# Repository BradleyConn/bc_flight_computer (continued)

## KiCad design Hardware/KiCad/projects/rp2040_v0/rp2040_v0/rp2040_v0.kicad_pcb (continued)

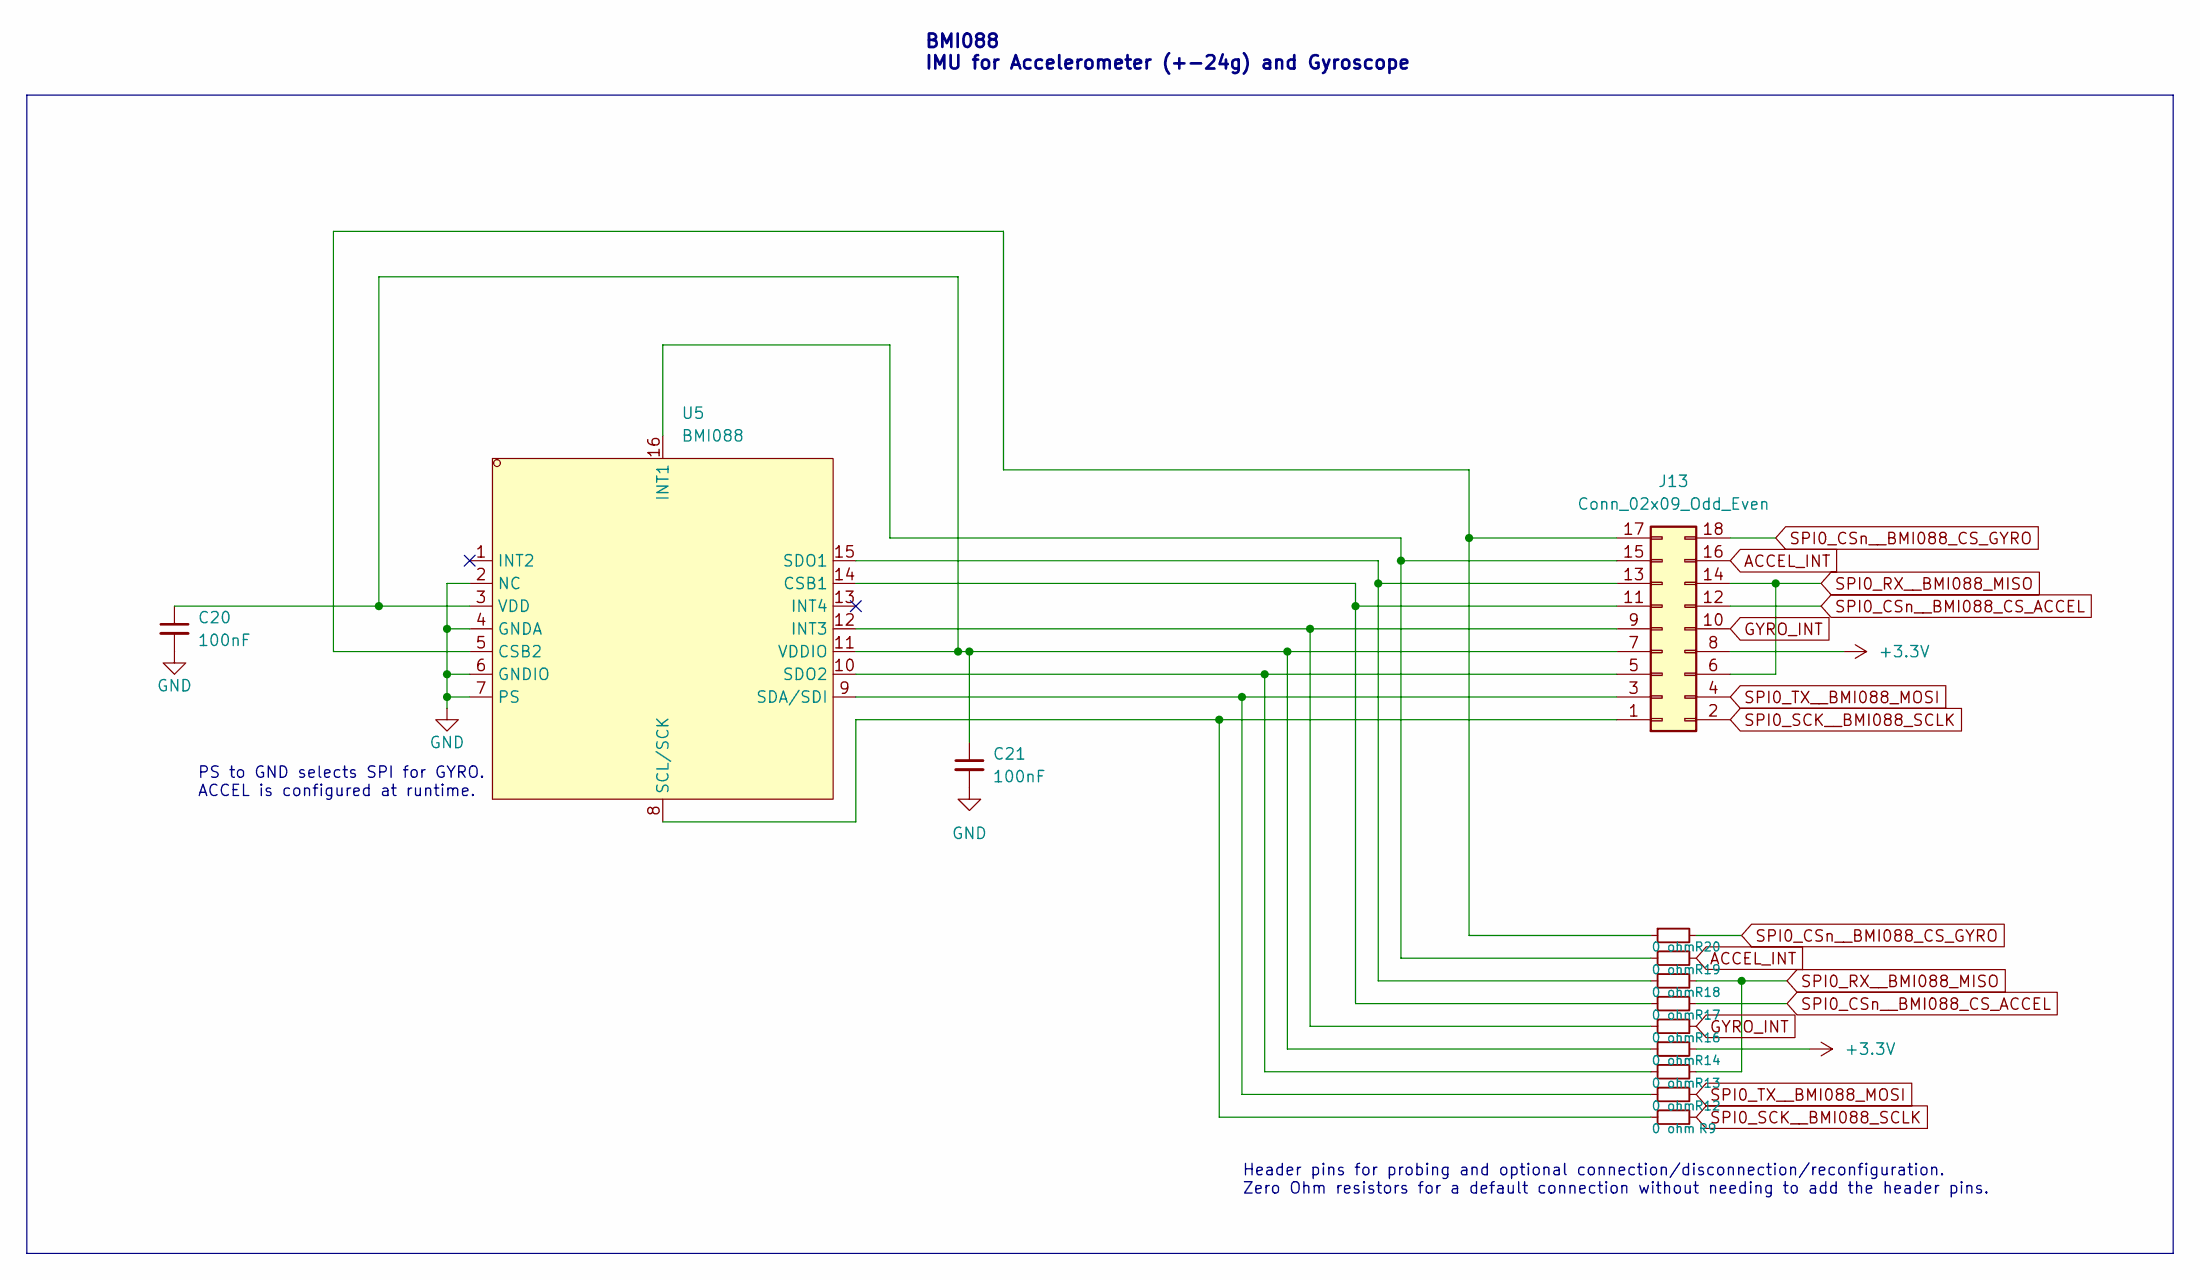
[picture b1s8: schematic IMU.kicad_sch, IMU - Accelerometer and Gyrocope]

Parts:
C20, C21: 100nF; C_0402_1005Metric; LCSC Part C307331
J13: Conn_02x09_Odd_Even; PinHeader_2x09_P2.54mm_Vertical
R9, R12, R13, R14, R16, R17, R18, R19, R20: 0 ohm; R_0402_1005Metric; LCSC Part C17168
U5: BMI088; LGA-16_L4.5-W3.0-P0.50-BL; LCSC Part C194919

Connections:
+3.3V: J13.8, R14.2; also elsewhere on the board
ACCEL_INT: J13.16, R19.2; also elsewhere on the board
GND: C20.2, C21.2, U5.2 (NC), U5.4 (GNDA), U5.6 (GNDIO), U5.7 (PS); also elsewhere on the board
GYRO_INT: J13.10, R16.2; also elsewhere on the board
unnamed: C20.1, C21.1, J13.7, R14.1, U5.3 (VDD), U5.11 (VDDIO)
unnamed: J13.1, R9.1, U5.8 (SCL/SCK)
unnamed: J13.3, R12.1, U5.9 (SDA/SDI)
unnamed: J13.5, R13.1, U5.10 (SDO2)
unnamed: J13.9, R16.1, U5.12 (INT3)
unnamed: J13.11, R17.1, U5.14 (CSB1)
unnamed: J13.13, R18.1, U5.15 (SDO1)
unnamed: J13.15, R19.1, U5.16 (INT1)
unnamed: J13.17, R20.1, U5.5 (CSB2)
SPI0_CSn__BMI088_CS_ACCEL: J13.12, R17.2; also elsewhere on the board
SPI0_CSn__BMI088_CS_GYRO: J13.18, R20.2; also elsewhere on the board
SPI0_RX__BMI088_MISO: J13.6, J13.14, R13.2, R18.2; also elsewhere on the board
SPI0_SCK__BMI088_SCLK: J13.2, R9.2; also elsewhere on the board
SPI0_TX__BMI088_MOSI: J13.4, R12.2; also elsewhere on the board

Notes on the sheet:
PS to GND selects SPI for GYRO. ACCEL is configured at runtime.
Header pins for probing and optional connection/disconnection/reconfiguration. Zero Ohm resistors for a default connection without needing to add the header pins.
BMI088 IMU for Accelerometer (+-24g) and Gyroscope

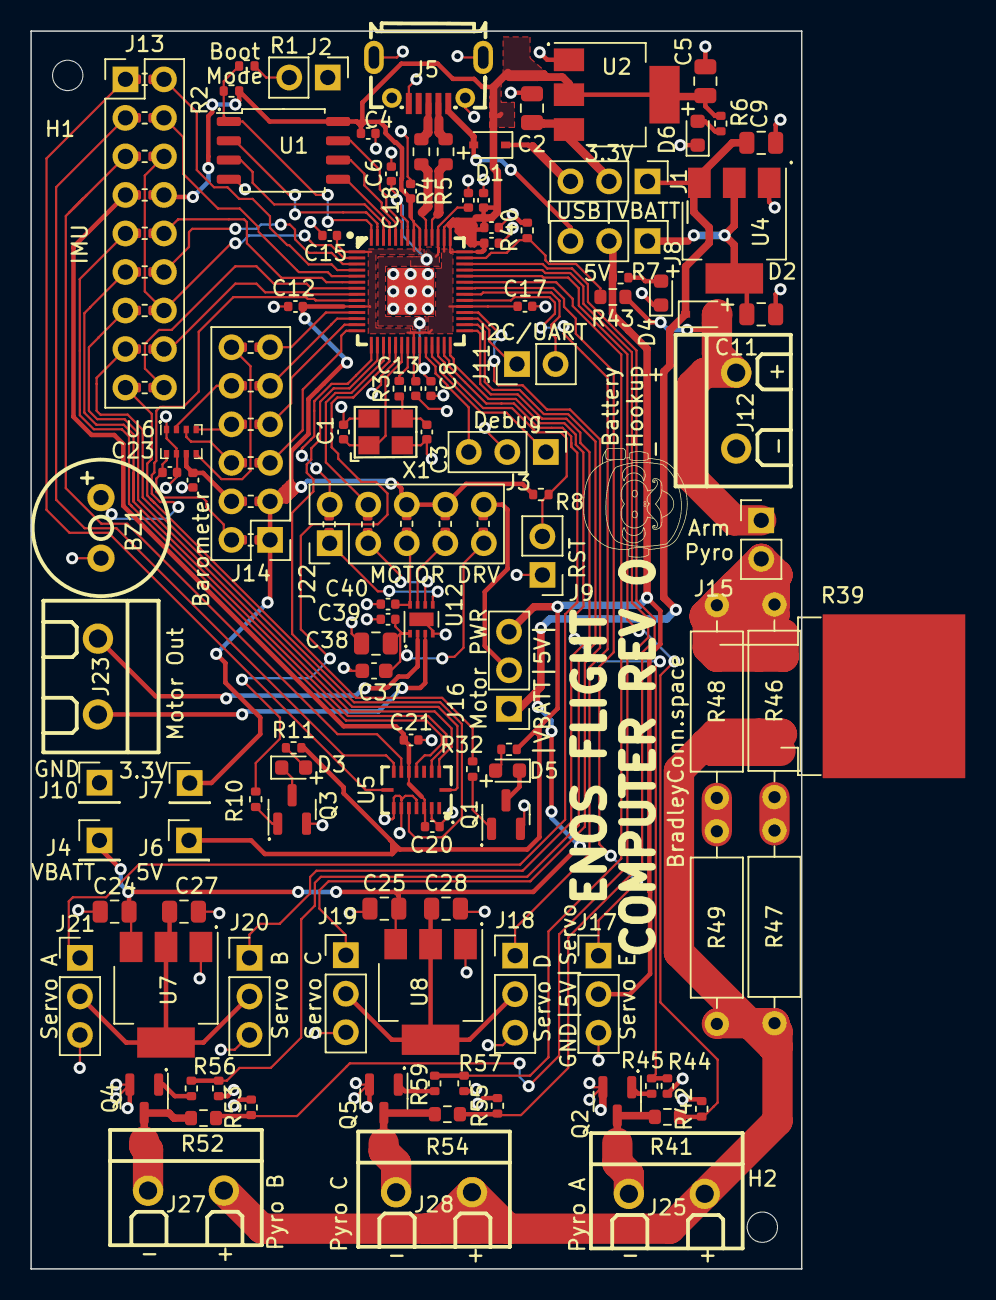
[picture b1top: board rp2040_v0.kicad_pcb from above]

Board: 2 copper layers, 50.8 x 81.6 mm, 131 parts (0 on the bottom side), 100 nets.

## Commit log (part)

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2023-01-29 Add lcsc symbols and footprints
2023-01-29 Add schematic and gitignore file
2023-01-29 Fixup easyeda2kicad environment variable paths
2023-01-29 Fix some wrong schematic footprints.
2023-01-29 Rename untitled to IMU
2023-01-29 PCB is WAY too big. Start optimizing and update to v0.1.
    Removes reset push button
2023-01-29 Remove level shifter from design
2023-01-29 Make the IMU header smaller
2023-01-29 Change arming screw terminal to jumper
2023-01-29 Remove pyro channel D
2023-01-29 Remove telelmetry screw terminal - leave header pin
2023-01-30 Add new smaller red led part
2023-01-30 Swap out ws2812b led for small red and green led.
2023-01-30 Make mounting holes smaller. Remove and combine extra power headers
2023-01-30 Somehow the power rail led indicator got changed to 5v. Change it back
2023-01-30 Remove extra servo LDO. Nothing else is on that 5V rail so share the normal one.
2023-01-30 Remove flash spi testpoints. They're pretty big by default.
2023-01-30 put power pins on separate headers so you can't accidently attache a jumper and short things.
2023-01-30 Remove reaction wheel LDO. Add jumper to select power source.
2023-01-30 Initial unrouted pcb layout
2023-01-30 Remove -Batt and just call it GND so it's less confusing in PCB
2023-01-30 Update the flash chip footprint to use default kicad instead of generated one. The 3d model was messed up and I wanted assurance the footprint was not the issue.
2023-01-30 Change net from global to net so it didn't change the name in pcb
2023-01-30 CRITICAL MISTAKE FOUND. FIXED. Flash was wired wrong. Add versioning sheet.
2023-01-30 Update sheets to say V0.2.
2023-01-30 Change LEDs to be kicad versions using kicad footprints for consistancy.
2023-01-30 Update leds and further layout work
2023-01-30 Change connector to be odd-even
2023-01-30 Add note on raw usb power to schematic
2023-01-30 witch led and pyro pins for easier routing
2023-01-30 update pcb with new pinout
2023-01-31 Change some header pin pinouts to make routing easier.
2023-01-31 Whoops - reconnect IMU pin that accidently got removed.
2023-01-31 MAKE SURE SAFTEY ARMING JUMPER IS BEFORE THE RESISTORS. Don't leave any hot wires exposed.
2023-01-31 Add net name to other side of temrination resistors for usb so it's easier to see in pcb.
2023-01-31 Moved reaction control wheel pin numbers around for easier routing.
2023-01-31 ON NO! I didn't realize the IMU is not in the center of the board and it really ought to be. What to do what to do...
2023-01-31 Update files to v0.3 and add new notes to version sheet.
2023-02-22 Rev 0 ready to ship! Had to move IMU so board got sloppy. IMU should be in the middle of the board. Glad I caught that.
2023-02-23 Some minor changes with footprint. Sent to JLCPCB. Official Rev 0!
2023-03-07 Add pico-sdk submodule
2023-04-21 Move the plus minus silkscreen on the bottom back into place.
2023-05-02 First simulation commit. Does some graphs of flight paths. No rocket control inputs yet
2023-05-04 Made a simulation2.py for experimentation
2023-05-04 Had to map to my own coordinate system but it looks like simulation2.py works!
2023-05-04 MAke everything in degrees. Matches other simulation exactly now.
2023-05-10 PID fixes
2023-05-10 Copy of pico examples setup with hello_world
2023-05-10 Update gitignore for all the cmake output
2023-05-10 Better project starting place.
2023-05-11 Prototyping pwm servo and led fades
2023-05-12 Servo drivers added
2023-05-13 add pwm_led driver
2023-05-13 Whoops forgot to add bsp
2023-05-15 Update pwm drivers to get channels by function using pins instead of params.
2023-05-16 Add BMP280 driver
2023-08-20 First pass working accel. Maybe Gyro too. Accel needed a dummy byte read.
2023-09-12 Added 3d model folder. Most models are still missing
2023-09-12 Add wip simulation3.py
2023-09-12 Add wip simulation.py
2023-09-12 Add old auto loading script before debugger was used
2023-09-12 Add cmake to readme
2023-12-16 Use bsp file defines for BMP and BMI sensors.
2023-12-16 Add range and bandwith to gyro init
2023-12-16 Change the digital servo speed to something appropriate - untested.
2023-12-17 Turn printing into helper functions in bmi088
2023-12-18 Make the line length longer for formatting
2023-12-18 Overhaul the bmi088 driver. Basically like new. Can read all registers and calulate values and print them.
2023-12-18 Remove unnecessary sleeps in bmi088 and increase clockrate to 10mhz
2023-12-19 Fix type compare warnings
2023-12-19 Turn on more warnings in CMakeLists.txt. Update .gitignore to include all build folders
2023-12-19 Add comment to the top of the BMI088 driver. Remove commented out code
2023-12-19 Format bmp280 - no code changes
2023-12-21 Update bmp280 driver. Remove humidty, and use style of bmi088
2023-12-22 Add thrust curve lookup of e12, and timekeeper classes
2023-12-22 Add buzzer driver
2024-01-08 Add a flash logging driver.
2024-01-08 Time flash writing and make a note of it in the header
2024-01-08 control_logic->system
2024-01-08 Add data container to store and print all telemetery
2024-01-08 from data_container to telemetry_container
2024-01-08 Add delay to bmi088 after init so first reg reading is accurate with new settings.
2024-01-08 Store telem in flash. Read it back next boot and print it with telem print functions.
2024-01-08 Turn off logging to flash every loop
2024-01-10 Move thrust curves to their own folder.
2024-01-17 Remove BMP delay and add/delete some comments. Add function to turn of servo.
2024-01-17 Add E9 thrust curve.
2024-01-17 Add gpio driver.
2024-01-17 Add a servo characterization test
2024-01-17 Add Orientation repo as a submodule
2024-01-17 Update Orientation submodule
2024-01-17 Add Orientation to cmake
2024-01-21 Update bmi driver to use interrupt signals for proper data frequency. Update data rates
2024-01-21 Add absolute time to timekeeper
2024-01-21 Remove sleep delay from bmp280
2024-01-21 Add orientation tests - dc bias is a thing with gyros. who knew
2024-01-21 Add calibration into the gyro driver
2024-01-30 AYYYY I KNOW THE ORIENTATION ROLL-PITCH-ROLL CALCULATION WORKS!!
2024-02-10 Add some wip baseline pressure stuff
2024-02-15 Add chute test!
2024-02-15 Add printing via usb
2024-02-16 Update the servo drivers to be the correct range... Add an integated offset
2024-02-16 Make gyro calibration one variable
2024-02-16 REAL working orientation - verified
2024-02-16 Fix a bug in the gyro calibration that I just introduced
2024-02-16 Remove printing in servo and format it.
2024-02-16 Add timekeeper delta ms and delta seconds.
2024-02-16 HUGE commit! Add the control loop logic. Verified up to quaternion_orientation which is the biggest chunk
2024-02-20 Make torque to tvc angle float instead of int
2024-02-20 Make a simple delay version of the ejection test
2024-02-20 Outline of a state machine
2024-02-20 Add blocking play sounds in buzzer.
2024-02-21 Start of state machine and control loop coming together and compiling
2024-02-22 Not tuned correctly I'm sure but should be a working conrtol loop
2024-02-22 Add parachute obj
2024-02-24 The flight code for better or for worse!!!
